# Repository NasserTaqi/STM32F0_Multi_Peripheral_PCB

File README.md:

# STM32F0 Multi Peripheral PCB
This is a PCB project built around an STM32F0 which includes multiple peripherals.

## Components
-	STM32F0 MCU
-	USB C 2.0 connection + ESD protection
-	3.3V power regulator LDO
-	Li-Ion/ Li-Pol battery charger
-	External flash memory
-	GPIO extender
-	Accelerometer + Gyroscope IC
-	Motor Controller IC
-	RGB LED
-	SWD Connector

## Board Setup
It is a 4-layer board with the following stack-up:

Layer: 1	SIGNAL

Layer: 2	GND

Layer: 3	POWER

Layer: 4	SIGNAL

### PCB Schematic:

### PCB Layout:

### PCB 3D view:

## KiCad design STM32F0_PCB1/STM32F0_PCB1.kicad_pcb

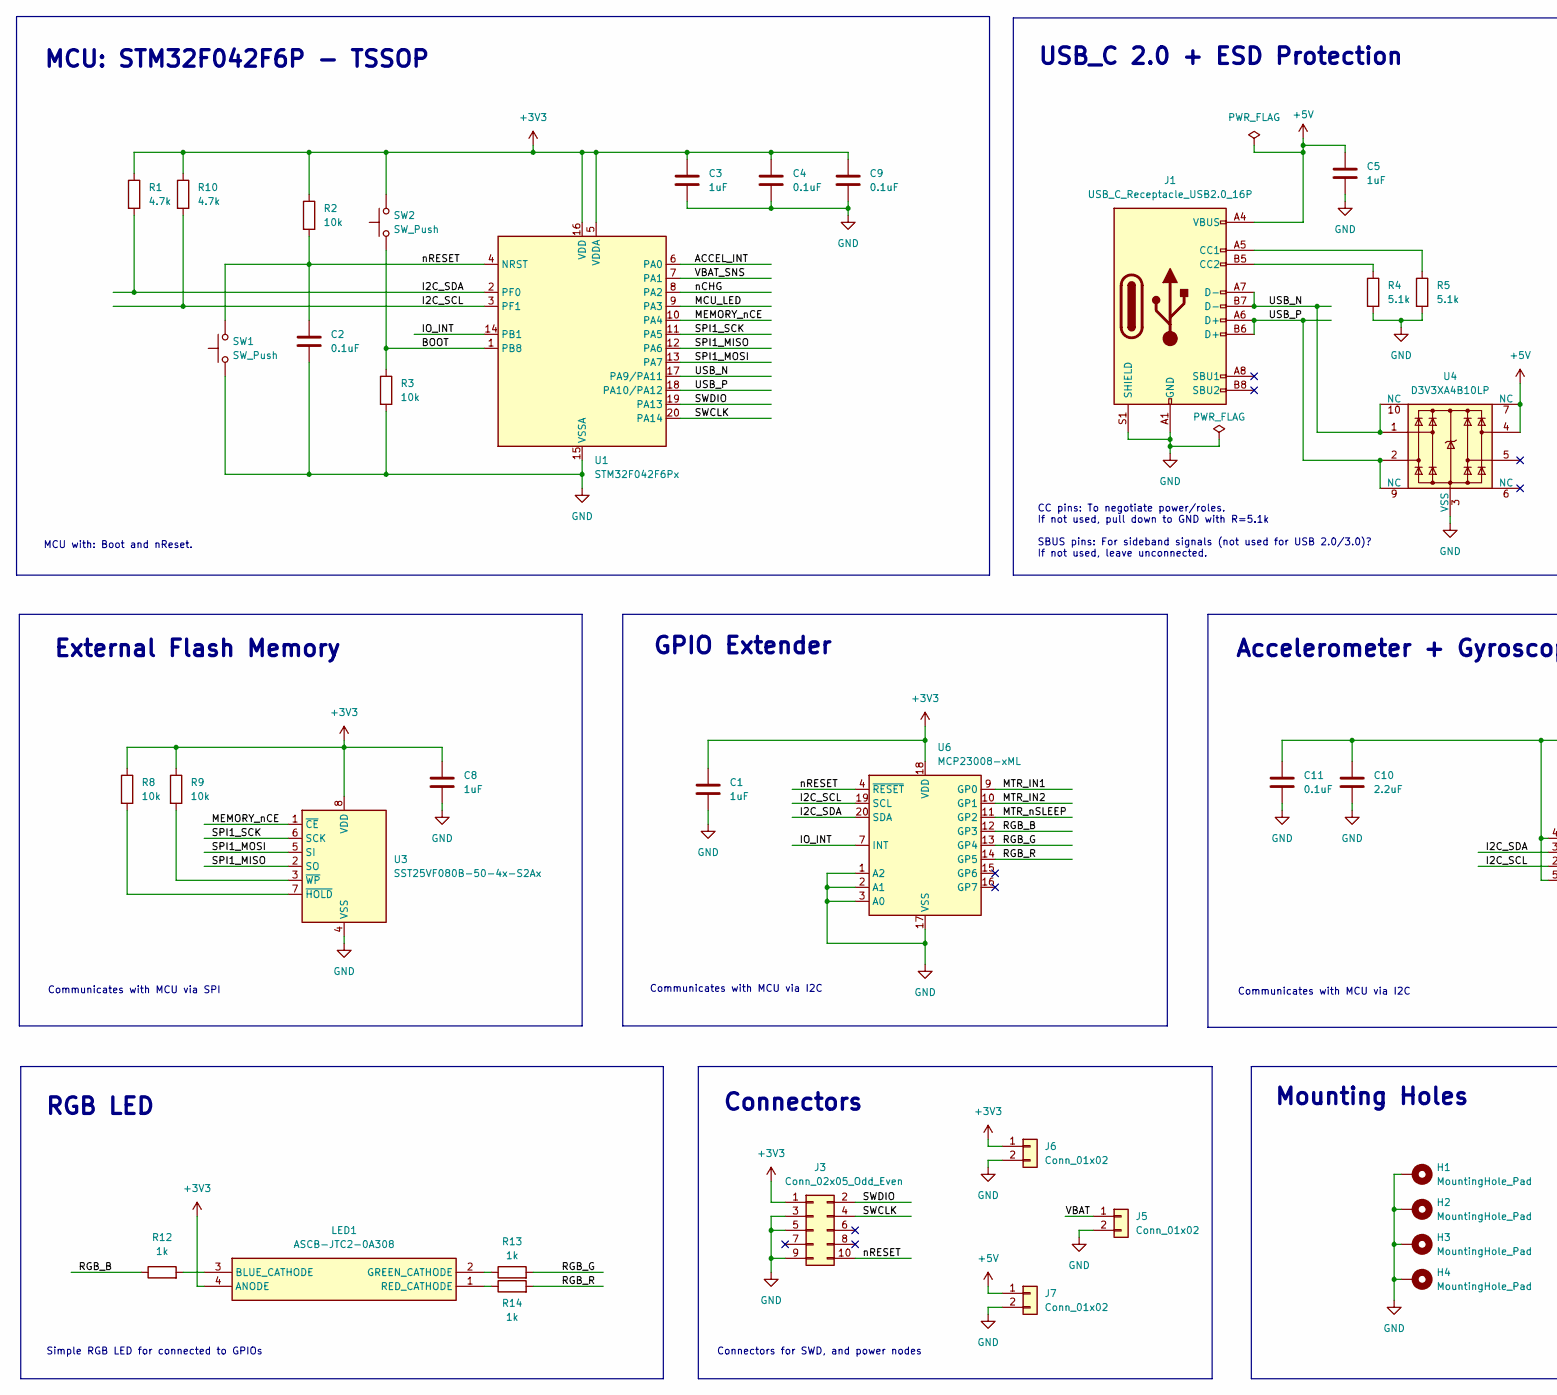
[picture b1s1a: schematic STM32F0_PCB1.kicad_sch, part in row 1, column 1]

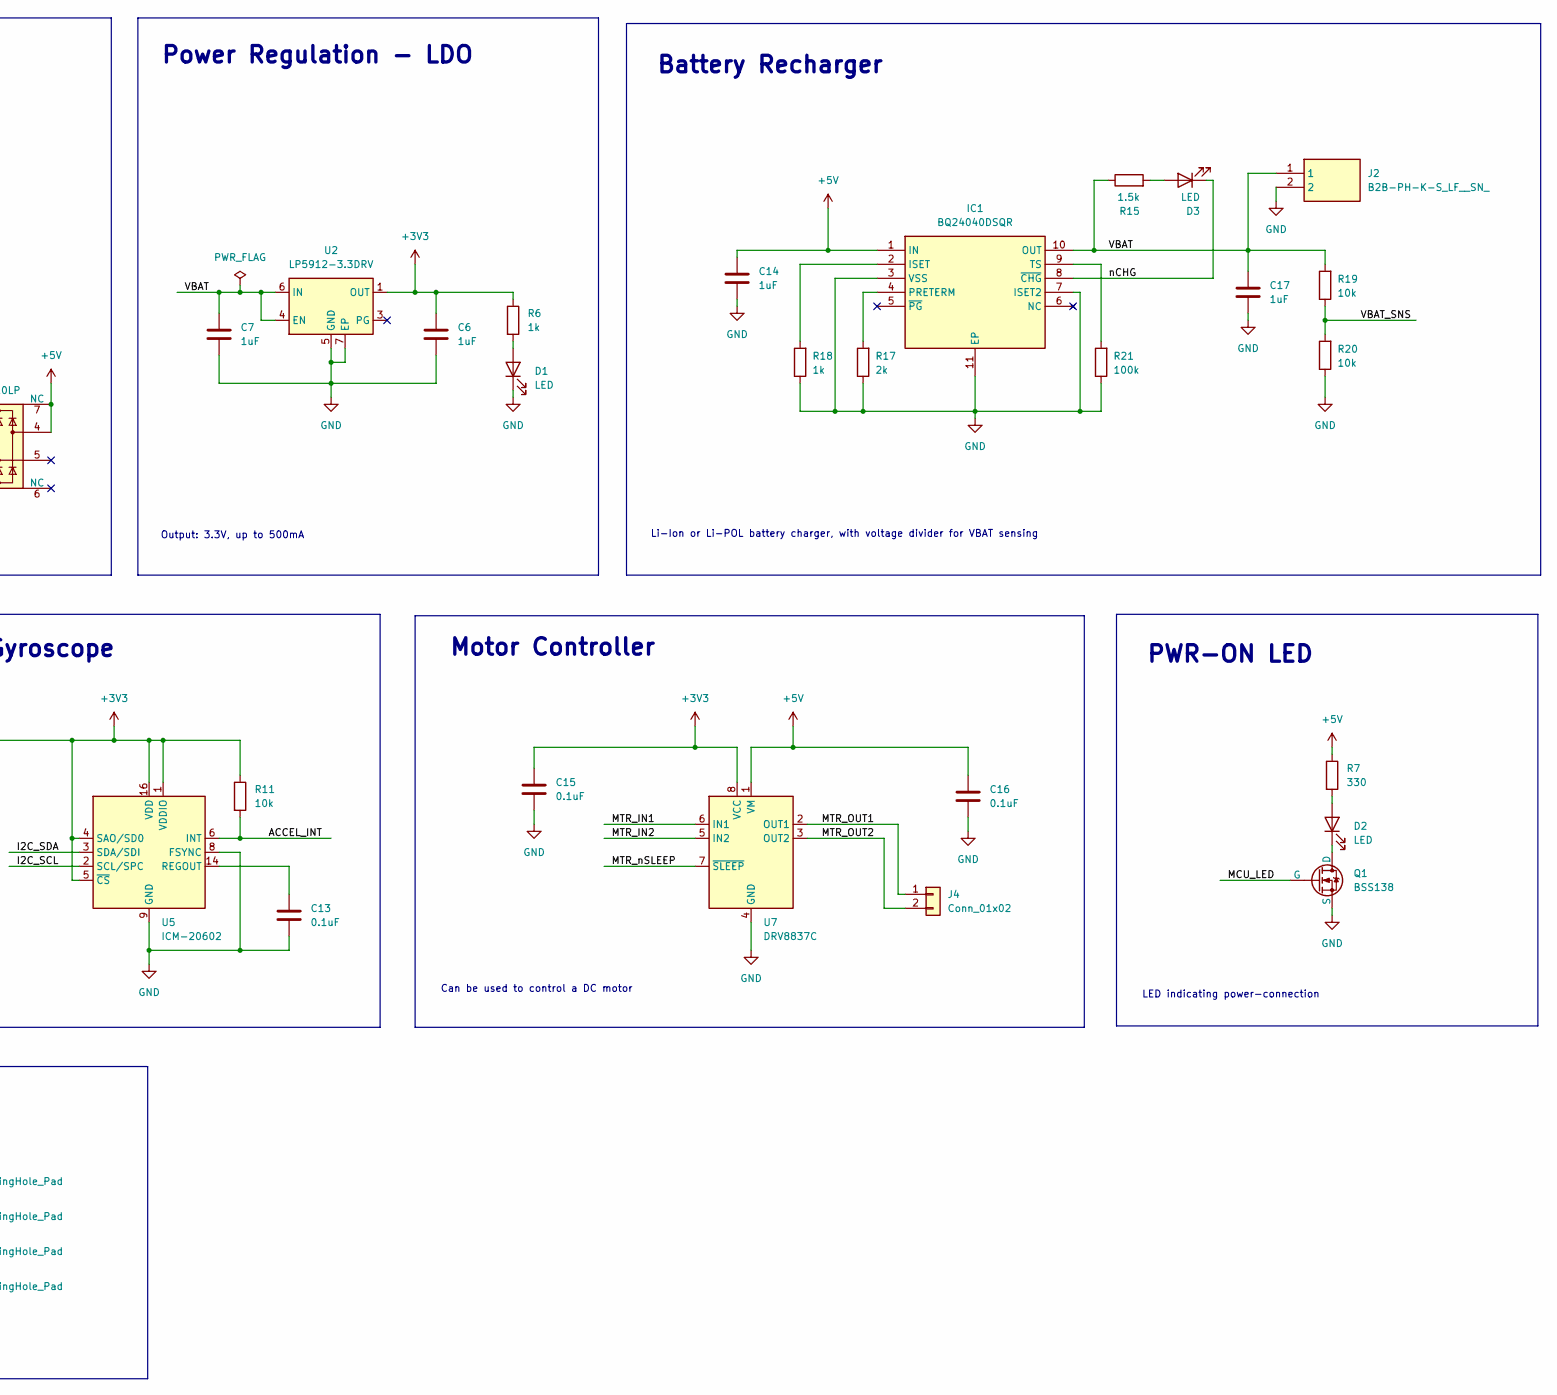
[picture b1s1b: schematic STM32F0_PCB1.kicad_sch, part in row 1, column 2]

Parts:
C1, C5, C6, C7, C8, C14, C17: 1uF; C_0805_2012Metric; Manufacturer Part Number KGM21AR51E105KL
C2, C11, C13, C15, C16: 0.1uF; C_0805_2012Metric; Manufacturer Part Number 885012207098
C3: 1uF; C_0603_1608Metric; Manufacturer Part Number MSASE168SB5105KTNA01
C4, C9: 0.1uF; C_0603_1608Metric; Manufacturer Part Number CC0603JRX7R9BB104
C10: 2.2uF; C_0805_2012Metric; Manufacturer Part Number GXT21BR71C225KE01L
D1, D2, D3: LED; LED_0805_2012Metric; Manufacturer Part Number HSMW-C170-U0000
H1, H2, H3, H4: MountingHole_Pad; MountingHole_2.2mm_M2_Pad_Via
IC1: BQ24040DSQR; SON40P200X200X80-11N; Mouser Part Number 595-BQ24040DSQR
J1: USB_C_Receptacle_USB2.0_16P; USB_C_Receptacle_GCT_USB4105-xx-A_16P_TopMnt_Horizontal; Manufacturer Part Number USB4930-00-A
J2: B2B-PH-K-S_LF__SN_; SHDR2W50P0X200_1X2_590X450X600P; Mouser Part Number 306-B2BPHKSLFSNPP
J3: Conn_02x05_Odd_Even; PinHeader_2x05_P1.27mm_Vertical_SMD; Manufacturer Part Number 10129381-910004BLF
J4, J5, J6, J7: Conn_01x02; PinHeader_1x02_P2.54mm_Vertical; Manufacturer Part Number 826646-2
LED1: ASCB-JTC2-0A308; ASCBJTC20A308; Mouser Part Number 630-ASCB-JTC2-0A308
Q1: BSS138; SOT-23; Manufacturer Part Number BSS138
R1, R10: 4.7k; R_0805_2012Metric; Manufacturer Part Number AC0805JR-134K7L
R2, R3, R8, R9, R11, R19, R20: 10k; R_0805_2012Metric; Manufacturer Part Number RE0805FRE1010KL
R4, R5: 5.1k; R_0805_2012Metric; Manufacturer Part Number RC0805JR-105K1L
R6, R12, R13, R14, R18: 1k; R_0805_2012Metric; Manufacturer Part Number SR0805FR-7W1KL
R7: 330; R_0805_2012Metric; Manufacturer Part Number ERJ-PC6B3300V
R15: 1.5k; R_0805_2012Metric; Manufacturer Part Number AF0805FR-071K5L
R17: 2k; R_0805_2012Metric; Manufacturer Part Number SR0805JR-072KL
R21: 100k; R_0805_2012Metric; Manufacturer Part Number TR0805NR-07100KL
SW1, SW2: SW_Push; SW_SPST_PTS810; Manufacturer Part Number PTS810SJK250SMTR LFS
U1: STM32F042F6Px; TSSOP-20_4.4x6.5mm_P0.65mm; Manufacturer Part Number STM32F042F6P6
U2: LP5912-3.3DRV; WSON-6-1EP_2x2mm_P0.65mm_EP1x1.6mm_ThermalVias; Manufacturer Part Number LP5912-3.3DRVT
U3: SST25VF080B-50-4x-S2Ax; SOIC-8_5.3x5.3mm_P1.27mm; Manufacturer Part Number SST25VF080B-50-4C-S2AF
U4: D3V3XA4B10LP; Diodes_UDFN-10_1.0x2.5mm_P0.5mm; Manufacturer Part Number D3V3XA4B10LP-7
U5: ICM-20602; LGA-16_3x3mm_P0.5mm_LayoutBorder3x5y; Manufacturer Part Number ICM-20602
U6: MCP23008-xML; QFN-20-1EP_4x4mm_P0.5mm_EP2.7x2.7mm; Manufacturer Part Number MCP23008-E/ML
U7: DRV8837C; WSON-8-1EP_2x2mm_P0.5mm_EP0.9x1.6mm; Manufacturer Part Number DRV8837CDSGR

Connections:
+3V3: C1.1, C3.1, C4.1, C6.1, C8.1, C9.1, C10.1, C11.1, C15.1, J3.1, J6.1, LED1.4 (ANODE), R1.1, R2.1, R6.1, R8.1, R9.1, R10.1, R11.1, SW2.2, U1.5 (VDDA), U1.16 (VDD), U2.1 (OUT), U3.8 (VDD), U5.1 (VDDIO), U5.4 (SAO/SD0), U5.5 (~CS), U5.16 (VDD), U6.18 (VDD), U7.8 (VCC)
+5V: C5.1, C14.1, C16.1, IC1.1 (IN), J1.A4 (VBUS), J1.A9 (VBUS), J1.B4 (VBUS), J1.B9 (VBUS), J7.1, R7.1, U4.4, U4.7 (NC), U7.1 (VM)
/ACCEL_INT: R11.2, U1.6 (PA0), U5.6 (INT)
/BOOT: R3.1, SW2.1, U1.1 (PB8)
/I2C_SCL: R10.2, U1.3 (PF1), U5.2 (SCL/SPC), U6.19 (SCL)
/I2C_SDA: R1.2, U1.2 (PF0), U5.3 (SDA/SDI), U6.20 (SDA)
/IO_INT: U1.14 (PB1), U6.7 (INT)
/MCU_LED: Q1.2 (G), U1.9 (PA3)
/MEMORY_nCE: U1.10 (PA4), U3.1 (~CE)
/MTR_IN1: U6.9 (GP0), U7.6 (IN1)
/MTR_IN2: U6.10 (GP1), U7.5 (IN2)
/MTR_OUT1: J4.1, U7.2 (OUT1)
/MTR_OUT2: J4.2, U7.3 (OUT2)
/MTR_nSLEEP: U6.11 (GP2), U7.7 (~SLEEP)
/RGB_B: R12.1, U6.12 (GP3)
/RGB_G: R13.2, U6.13 (GP4)
/RGB_R: R14.2, U6.14 (GP5)
/SPI1_MISO: U1.12 (PA6), U3.2 (SO)
/SPI1_MOSI: U1.13 (PA7), U3.5 (SI)
/SPI1_SCK: U1.11 (PA5), U3.6 (SCK)
/SWCLK: J3.4, U1.20 (PA14)
/SWDIO: J3.2, U1.19 (PA13)
/USB_N: J1.A7 (D-), J1.B7 (D-), U1.17 (PA9/PA11), U4.1, U4.10 (NC)
/USB_P: J1.A6 (D+), J1.B6 (D+), U1.18 (PA10/PA12), U4.2, U4.9 (NC)
/VBAT: C7.1, C17.1, IC1.10 (OUT), J2.1, J5.1, R15.1, R19.2, U2.4 (EN), U2.6 (IN)
/VBAT_SNS: R19.1, R20.2, U1.7 (PA1)
/nCHG: D3.1 (K), IC1.8 (~CHG), U1.8 (PA2)
/nRESET: C2.1, J3.10, R2.2, SW1.2, U1.4 (NRST), U6.4 (~RESET)
GND: C1.2, C2.2, C3.2, C4.2, C5.2, C6.2, C7.2, C8.2, C9.2, C10.2, C11.2, C13.2, C14.2, C15.2, C16.2, C17.2, D1.1 (K), H1.1, H2.1, H3.1, H4.1, IC1.3 (VSS), IC1.7 (ISET2), IC1.11 (EP), J1.A1 (GND), J1.A12 (GND), J1.B1 (GND), J1.B12 (GND), J1.S1 (SHIELD), J2.2, J3.3, J3.5, J3.9, J5.2, J6.2, J7.2, Q1.3 (S), R3.2, R4.2, R5.2, R17.1, R18.1, R20.1, R21.1, SW1.1, U1.15 (VSSA), U2.5 (GND), U2.7 (EP), U3.4 (VSS), U4.3 (VSS), U4.8 (VSS), U5.8 (FSYNC), U5.9 (GND), U5.10 (GND), U5.11 (GND), U5.12 (GND), U5.13 (GND), U5.15 (GND), U6.1 (A2), U6.2 (A1), U6.3 (A0), U6.17 (VSS), U7.4 (GND), U7.9 (GND)
unnamed: D1.2 (A), R6.2
unnamed: D2.2 (A), R7.2
unnamed: D2.1 (K), Q1.1 (D)
unnamed: D3.2 (A), R15.2
unnamed: IC1.2 (ISET), R18.2
unnamed: IC1.4 (PRETERM), R17.2
unnamed: IC1.9 (TS), R21.2
unnamed: J1.A5 (CC1), R5.1
unnamed: J1.B5 (CC2), R4.1
unnamed: LED1.3 (BLUE_CATHODE), R12.2
unnamed: LED1.2 (GREEN_CATHODE), R13.1
unnamed: LED1.1 (RED_CATHODE), R14.1
unnamed: R8.2, U3.7 (~HOLD)
unnamed: R9.2, U3.3 (~WP)
unnamed: C13.1, U5.14 (REGOUT)

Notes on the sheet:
Power Regulation - LDO
Communicates with MCU via I2C
CC pins: To negotiate power/roles. If not used, pull down to GND with R=5.1k SBUS pins: For sideband signals (not used for USB 2.0/3.0)? If not used, leave unconnected.
USB_C 2.0 + ESD Protection
Communicates with MCU via SPI
MCU: STM32F042F6P - TSSOP
GPIO Extender
LED indicating power-connection
RGB LED
Can be used to control a DC motor
Output: 3.3V, up to 500mA
Motor Controller
Simple RGB LED for connected to GPIOs
PWR-ON LED
Li-Ion or Li-POL battery charger, with voltage divider for VBAT sensing
Accelerometer + Gyroscope
External Flash Memory
Battery Recharger
Mounting Holes
Connectors
MCU with: Boot and nReset.
Connectors for SWD, and power nodes

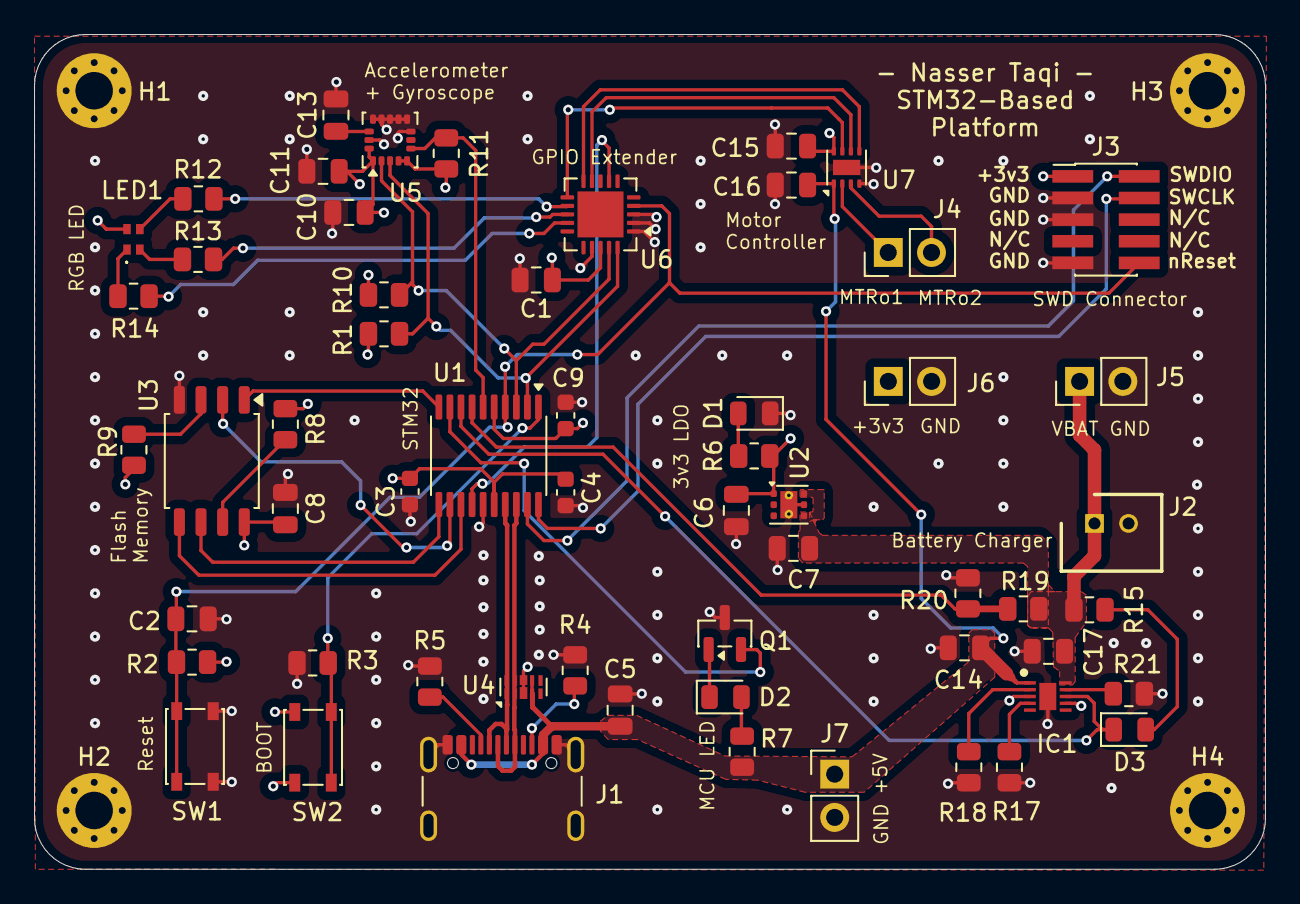
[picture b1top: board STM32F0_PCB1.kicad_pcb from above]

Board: 4 copper layers, 72.3 x 49.0 mm, 62 parts (0 on the bottom side), 44 nets.

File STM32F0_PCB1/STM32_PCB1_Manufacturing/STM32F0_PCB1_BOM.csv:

"Reference","Qty","Value","Footprint","Datasheet","Distributor Link","Manufacturer","Manufacturer Part Number"
"C1,C5,C6,C7,C8,C14,C17","7","1uF","Capacitor_SMD:C_0805_2012Metric","~","https://www.mouser.dk/ProductDetail/KYOCERA-AVX/KGM21AR51E10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","KYOCERA AVX","KGM21AR51E105KL"
"C2,C11,C13,C15,C16","5","0.1uF","Capacitor_SMD:C_0805_2012Metric","~","https://www.mouser.dk/ProductDetail/Wurth-Elektronik/8850122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","Wurth Elektronik","885012207098"
"C3","1","1uF","Capacitor_SMD:C_0603_1608Metric","~","https://www.mouser.dk/ProductDetail/TAIYO-YUDEN/MSASE168SB51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","TAIYO YUDEN","MSASE168SB5105KTNA01 "
"C4,C9","2","0.1uF","Capacitor_SMD:C_0603_1608Metric","~","https://www.mouser.dk/ProductDetail/YAGEO/CC0603JRX7R9BB104?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","YAGEO","CC0603JRX7R9BB104"
"C10","1","2.2uF","Capacitor_SMD:C_0805_2012Metric","~","https://www.mouser.dk/ProductDetail/Murata-Electronics/GXT21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","Murata Electronics","GXT21BR71C225KE01L "
"D1,D2,D3","3","LED","LED_SMD:LED_0805_2012Metric","~","https://www.mouser.dk/ProductDetail/Broadcom-Avago/HSMW-C170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","Boradcom/Avago","HSMW-C170-U0000"
"H1,H2,H3,H4","4","MountingHole_Pad","MountingHole:MountingHole_2.2mm_M2_Pad_Via","~","","",""
"IC1","1","BQ24040DSQR","Samacsys:SON40P200X200X80-11N","http://www.ti.com/lit/gpn/bq24040","https://www.mouser.dk/ProductDetail/Texas-Instruments/BQ2404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","Texas Instruments","BQ24040DSQR"
"J1","1","USB_C_Receptacle_USB2.0_16P","Connector_USB:USB_C_Receptacle_GCT_USB4105-xx-A_16P_TopMnt_Horizontal","https://www.usb.org/sites/default/files/documents/usb_type-c.zip","https://www.mouser.dk/ProductDetail/GCT/USB4930-00-A?qs=vcFy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","GCT","USB4930-00-A"
"J2","1","B2B-PH-K-S_LF__SN_","Samacsys:SHDR2W50P0X200_1X2_590X450X600P","https://datasheet.lcsc.com/szlcsc/JST-Sales-America-B2B-PH-K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","https://www.mouser.dk/ProductDetail/JST-Commercial/B2B-PH-K-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","JST Commercial","B2B-PH-K-S(LF)(SN)"
"J3","1","Conn_02x05_Odd_Even","Connector_PinHeader_1.27mm:PinHeader_2x05_P1.27mm_Vertical_SMD","~","https://www.mouser.dk/ProductDetail/Amphenol-FCI/10129381-91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","Amphenol FCI","10129381-910004BLF"
"J4,J5,J6,J7","4","Conn_01x02","Connector_PinHeader_2.54mm:PinHeader_1x02_P2.54mm_Vertical","~","https://www.mouser.dk/ProductDetail/TE-Connectivity/826646-2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","TE Connectivity","826646-2"
"LED1","1","ASCB-JTC2-0A308","Samacsys:ASCBJTC20A308","https://docs.broadcom.com/doc/ASCB-JTC2-0A308-1615-Tricolor-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","https://www.mouser.dk/ProductDetail/Broadcom-Avago/ASCB-JTC2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","Braodcom/Avago","ASCB-JTC2-0A308"
"Q1","1","BSS138","Package_TO_SOT_SMD:SOT-23","https://www.mouser.dk/datasheet/3/175/1/BSS138.pdf","https://www.mouser.dk/ProductDetail/onsemi/BSS138?qs=HK%252B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","onsemi","BSS138"
"R1,R10","2","4.7k","Resistor_SMD:R_0805_2012Metric","~","https://www.mouser.dk/ProductDetail/YAGEO/AC0805JR-134K7L?qs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","YAGEO","AC0805JR-134K7L"
"R2,R3,R8,R9,R11,R19,R20","7","10k","Resistor_SMD:R_0805_2012Metric","~","https://www.mouser.dk/ProductDetail/YAGEO/RE0805FRE1010KL?qs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","YAGEO","RE0805FRE1010KL"
"R4,R5","2","5.1k","Resistor_SMD:R_0805_2012Metric","~","https://www.mouser.dk/ProductDetail/YAGEO/RC0805JR-105K1L?qs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","YAGEO","RC0805JR-105K1L"
"R6,R12,R13,R14,R18","5","1k","Resistor_SMD:R_0805_2012Metric","~","https://www.mouser.dk/ProductDetail/YAGEO/SR0805FR-7W1KL?qs=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","YAGEO","SR0805FR-7W1KL"
"R7","1","330","Resistor_SMD:R_0805_2012Metric","~","https://www.mouser.dk/ProductDetail/Panasonic/ERJ-PC6B3300V?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","Panasonic","ERJ-PC6B3300V "
"R15","1","1.5k","Resistor_SMD:R_0805_2012Metric","~","https://www.mouser.dk/ProductDetail/YAGEO/AF0805FR-071K5L?qs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","YAGEO","AF0805FR-071K5L"
"R17","1","2k","Resistor_SMD:R_0805_2012Metric","~","https://www.mouser.dk/ProductDetail/YAGEO/SR0805JR-072KL?qs=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","YAGEO","SR0805JR-072KL"
"R21","1","100k","Resistor_SMD:R_0805_2012Metric","~","https://www.mouser.dk/ProductDetail/YAGEO/TR0805NR-07100KL?q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","YAGEO","TR0805NR-07100KL"
"SW1,SW2","2","SW_Push","Button_Switch_SMD:SW_SPST_PTS810","~","https://www.mouser.dk/ProductDetail/CK/PTS810SJK250SMTR-LFS?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","C&K","PTS810SJK250SMTR LFS"
"U1","1","STM32F042F6Px","Package_SO:TSSOP-20_4.4x6.5mm_P0.65mm","https://www.st.com/resource/en/datasheet/stm32f042f6.pdf","https://www.mouser.dk/ProductDetail/STMicroelectronics/STM32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","STMicroelectronics","STM32F042F6P6"
"U2","1","LP5912-3.3DRV","Package_SON:WSON-6-1EP_2x2mm_P0.65mm_EP1x1.6mm_ThermalVias","http://www.ti.com/lit/ds/symlink/lp5912.pdf","https://www.mouser.dk/ProductDetail/Texas-Instruments/LP5912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","Texas Instruments","LP5912-3.3DRVT"
"U3","1","SST25VF080B-50-4x-S2Ax","Package_SO:SOIC-8_5.3x5.3mm_P1.27mm","http://ww1.microchip.com/downloads/en/DeviceDoc/20005045C.pdf","https://www.mouser.dk/ProductDetail/Microchip-Technology/SST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","Microchip Technology","SST25VF080B-50-4C-S2AF"
"U4","1","D3V3XA4B10LP","Package_DFN_QFN:Diodes_UDFN-10_1.0x2.5mm_P0.5mm","https://www.diodes.com/assets/Datasheets/D3V3XA4B10LP.pdf","https://www.mouser.dk/ProductDetail/Diodes-Incorporated/D3V3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","Diodes Incorporated","D3V3XA4B10LP-7"
"U5","1","ICM-20602","Package_LGA:LGA-16_3x3mm_P0.5mm_LayoutBorder3x5y","http://www.invensense.com/wp-content/uploads/2016/10/DS-0001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","https://www.mouser.dk/ProductDetail/TDK-InvenSense/ICM-20602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","TDK InvenSense","ICM-20602"
"U6","1","MCP23008-xML","Package_DFN_QFN:QFN-20-1EP_4x4mm_P0.5mm_EP2.7x2.7mm","http://ww1.microchip.com/downloads/en/DeviceDoc/MCP23008-MCP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","https://eu.mouser.com/ProductDetail/Microchip-Technology/MCP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","Microchop Technology","MCP23008-E/ML"
"U7","1","DRV8837C","Package_SON:WSON-8-1EP_2x2mm_P0.5mm_EP0.9x1.6mm","http://www.ti.com/lit/ds/symlink/drv8837c.pdf","https://www.mouser.dk/ProductDetail/Texas-Instruments/DRV883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","Texas Instruments","DRV8837CDSGR"
